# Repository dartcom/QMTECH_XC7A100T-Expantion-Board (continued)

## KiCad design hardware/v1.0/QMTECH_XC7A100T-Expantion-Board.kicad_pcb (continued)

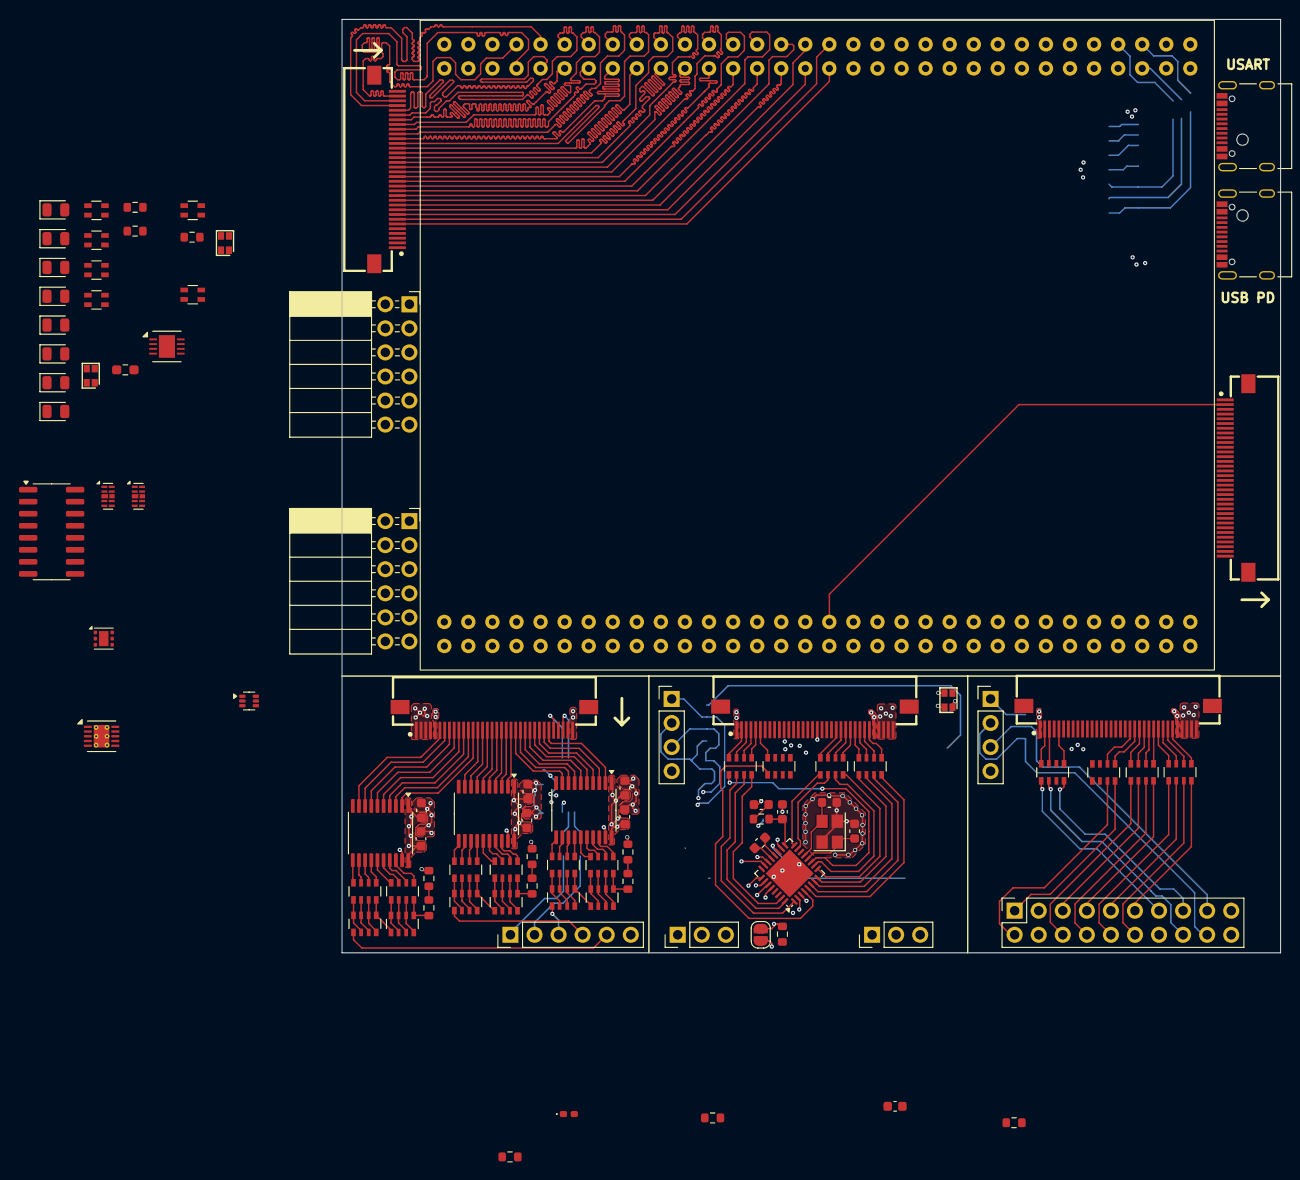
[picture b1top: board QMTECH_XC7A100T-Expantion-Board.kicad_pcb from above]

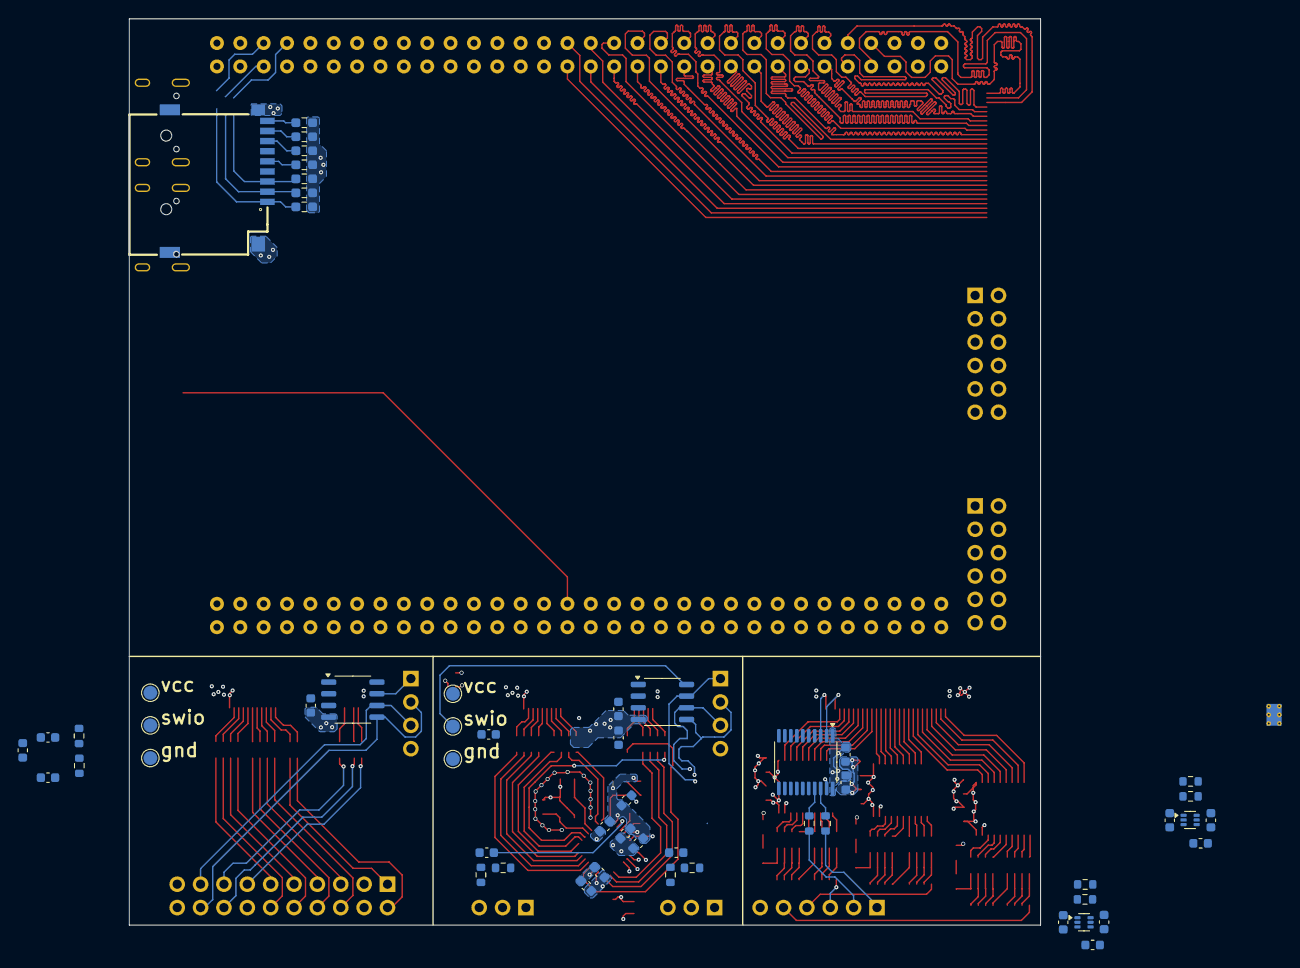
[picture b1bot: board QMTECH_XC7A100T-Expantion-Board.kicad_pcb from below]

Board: 4 copper layers, 99.1 x 98.5 mm, 148 parts (54 on the bottom side), 274 nets.

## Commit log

2025-04-28 initial push
2025-05-06 backup
2025-05-10 updated project to Kicad version 9.0
2025-06-12 added pmod connectors instead of leds
2025-06-13 first schematic iteration done
2025-06-13 did PORT0 routing
2025-06-16 redoing 3v3 regulators
2025-06-19 finished mainboard + progress on peripherals
2025-06-20 finished first draft, still DRC errors
2025-06-21 progress with drc errors
2025-06-22 first draft complete
2025-06-24 upped trace clearances
2025-06-24 changed some net classes colors
2025-06-24 fixed some length tuning patterns in PORT0
2025-06-25 fixed netclass rules and some length tunning patterns
2025-06-25 fixed netclass rules
2025-06-25 unconnected nets get default net class
2025-07-02 added etch thieving planes
2025-07-05 added proper copper thieving
2025-07-05 added version numbers + updated ibom & schematics
2025-07-05 added pin values on silkscreen
2025-07-05 generated first gerbers
2025-07-07 added tvs diode+changed inductors
2025-07-14 generated final gerbers for v1.0
2025-07-15 updated copper thieving
